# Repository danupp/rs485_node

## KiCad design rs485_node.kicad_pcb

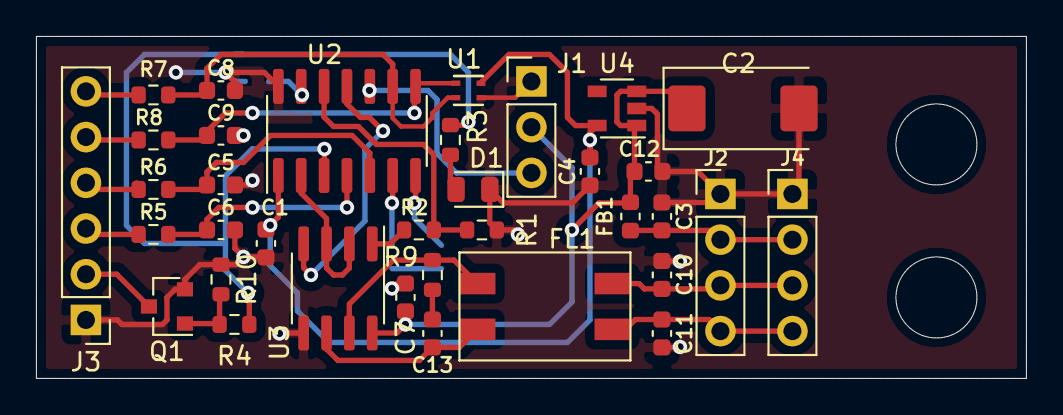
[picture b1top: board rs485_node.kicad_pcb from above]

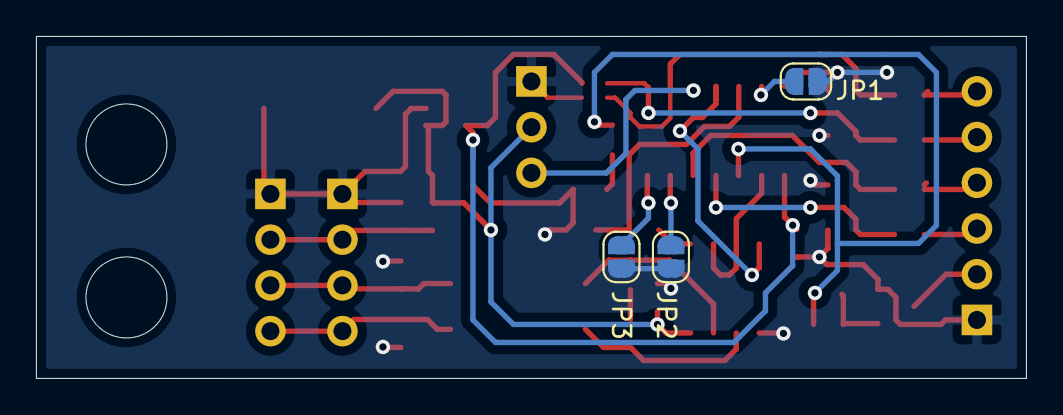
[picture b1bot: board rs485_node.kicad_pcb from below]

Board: 2 copper layers, 55.0 x 19.0 mm, 38 parts (3 on the bottom side), 29 nets.

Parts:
C1, C7, C12, C13: 100n; C_0603_1608Metric
C2: 47µ; CP_EIA-7343-31_Kemet-D
C3, C5, C6, C8, C9: 10n; C_0603_1608Metric
C4: 1u; C_0603_1608Metric
C10, C11: 1n; C_0603_1608Metric
D1: LED; LED_0805_2012Metric
FB1: 1000R@100; L_0603_1608Metric
FL1: WE-SL2
J1: Conn_01x03_Male; PinHeader_1x03_P2.54mm_Vertical
J2, J4: Conn_01x04_Male; PinHeader_1x04_P2.54mm_Vertical
J3: Conn_01x06_Male; PinHeader_1x06_P2.54mm_Vertical
JP1, JP2, JP3: SolderJumper_2_Open; SolderJumper-2_P1.3mm_Open_RoundedPad1.0x1.5mm
Q1: BC817; SOT-23
R1, R2, R3, R4, R5, R6, R7, R8, R9, R10: R; R_0603_1608Metric
U1: SHT40
U2: ATtiny214-SS; SOIC-14_3.9x8.7mm_P1.27mm
U3: ST485EBDR; SOIC-8_3.9x4.9mm_P1.27mm
U4: MIC5504-3.3YM5; SOT-23-5

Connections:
GND: C1.2, C2.2, C3.2, C4.2, C5.2, C6.2, C7.2, C8.2, C9.2, C10.2, C11.2, C12.2, D1.1, J1.1, J2.1, J3.1, J4.1, JP1.2, JP2.2, JP3.2, Q1.2, R1.2, R10.1, U1.3, U2.14, U3.5, U4.2
unnamed: C1.1, C4.1, U1.4, U2.1, U4.5
unnamed: C3.1, FB1.1, J2.2, J4.2
unnamed: C5.1, R6.2, U2.5
unnamed: C6.1, R5.2, U2.4
unnamed: C8.1, R7.2, U1.2, U2.9
unnamed: C9.1, R8.2, U1.1, U2.8
unnamed: C10.1, FL1.2, J2.3, J4.3
unnamed: C11.1, FL1.1, J2.4, J4.4
unnamed: C2.1, C7.1, C12.1, FB1.2, J1.2, U3.8, U4.1, U4.3
unnamed: C13.1, R9.2
unnamed: C13.2, FL1.4, U3.6
unnamed: D1.2, R3.1
unnamed: FL1.3, R9.1, U3.7
unnamed: J1.3, U2.10
unnamed: J3.2, Q1.3
unnamed: J3.3, R5.1
unnamed: J3.4, R6.1
unnamed: J3.5, R8.1
unnamed: J3.6, R7.1
unnamed: JP1.1, U2.13
unnamed: JP2.1, U2.6
unnamed: JP3.1, U2.7
unnamed: Q1.1, R4.1, R10.2
unnamed: R1.1, R2.2, U2.12
unnamed: R2.1, U3.1
unnamed: R3.2, R4.2, U2.3
unnamed: U2.2, U3.2, U3.3
unnamed: U2.11, U3.4

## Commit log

2021-03-23 Change to SHT40
2021-03-23 Added 3V3 LDO
2021-03-31 CM filter, termination etc.
2021-03-31 silk fix
2021-04-06 bjt, two conns
2021-04-15 new layout, removed dip-switch
